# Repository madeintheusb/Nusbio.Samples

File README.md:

Nusbio Samples
===============

Nusbio is a USB device that brings 8 GPIO pins (General Purpose Input Output), to the .NET Runtime and programming languages C#, VB.NET, F# and IronPython (like the Raspberry PI GPIO row for C and Python).

Nusbio also offers: 

* 8 GPIO pins
* I2C and SPI support
* One unique serial number
* 32 bytes of EEPROM (.NET ASCII string 32 char)

* ADC (Analog to digital converter) with extension
* DAC (Digital to analog converter) with extension 
* Supported Devices: LCD, OLED, LED Matrix, Sensors, RGB LED,...

# Copyright

http://www.MadeInTheUSB.net

Copyright (C) 2015, 2016 MadeInTheUSB LLC

# License 

    All samples and components classes are released under the MIT License.

    Permission is hereby granted, free of charge, to any person obtaining a copy of this software and 
    associated documentation files (the "Software"), to deal in the Software without restriction, 
    including without limitation the rights to use, copy, modify, merge, publish, distribute, 
    sublicense, and/or sell copies of the Software, and to permit persons to whom the Software is 
    furnished to do so, subject to the following conditions:

    The above copyright notice and this permission notice shall be included in all copies or substantial 
    portions of the Software.

    THE SOFTWARE IS PROVIDED "AS IS", WITHOUT WARRANTY OF ANY KIND, EXPRESS OR IMPLIED, INCLUDING BUT NOT 
    LIMITED TO THE WARRANTIES OF MERCHANTABILITY, FITNESS FOR A PARTICULAR PURPOSE AND NONINFRINGEMENT. 
    IN NO EVENT SHALL THE AUTHORS OR COPYRIGHT HOLDERS BE LIABLE FOR ANY CLAIM, DAMAGES OR OTHER LIABILITY, 
    WHETHER IN AN ACTION OF CONTRACT, TORT OR OTHERWISE, ARISING FROM, OUT OF OR IN CONNECTION WITH THE SOFTWARE 
    OR THE USE OR OTHER DEALINGS IN THE SOFTWARE.

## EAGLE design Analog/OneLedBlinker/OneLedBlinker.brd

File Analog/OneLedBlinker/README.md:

One Led Blinker
===============

Copyright (C) 2015 MadeInTheUSB.net

http://www.MadeInTheUSB.net

# License

Creative Commons - Attribution-ShareAlike 2.5 Generic (CC BY-SA 2.5)

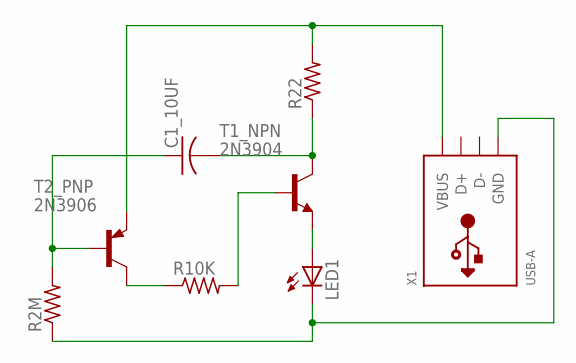
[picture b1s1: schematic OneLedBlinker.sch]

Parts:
C1_10UF: C-US025-030X050; C025-030X050
LED1: LED5MM
R2M, R10K, R22: R-US_0207/10; 0207/10
T1_NPN: 2N3904; TO92
T2_PNP: 2N3906; TO92
X1: USB-A; MOLEX_480371000

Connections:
unnamed: R22.2, T2_PNP.3 (E), X1.1 (VBUS)
unnamed: C1_10UF.2, R22.1, T1_NPN.1 (C)
unnamed: LED1.A, T1_NPN.3 (E)
unnamed: LED1.K (C), R2M.1, X1.4 (GND)
unnamed: C1_10UF.1, R2M.2, T2_PNP.2 (B)
unnamed: R10K.1, T2_PNP.1 (C)
unnamed: R10K.2, T1_NPN.2 (B)

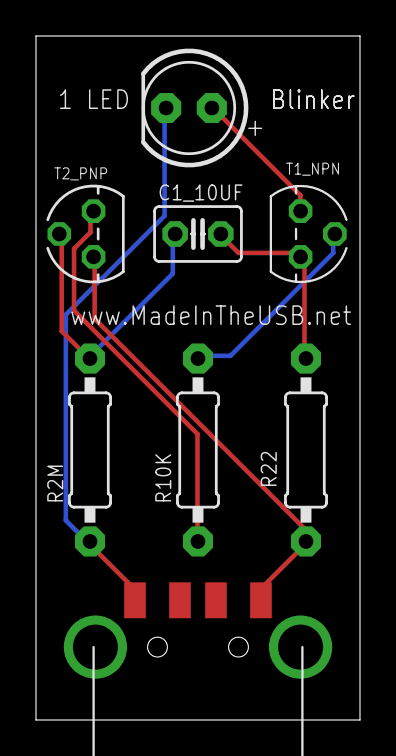
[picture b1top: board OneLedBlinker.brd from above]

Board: 2 copper layers, 18.0 x 38.0 mm, 8 parts (0 on the bottom side), 7 nets.

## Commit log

2016-04-07 :circus_tent: Added .gitattributes & .gitignore files
2016-04-07 Creation
2016-07-09 1.0.31 fixed web site on console
2016-07-09 1.0.32
2016-07-11 1.0.33
2016-07-11 Cleaning
2016-07-31 I2C interface cleaning and performance update
    I2C interface cleaning and performance update
2016-08-01 SPI clean up
2016-08-27 Change default addresss for I2C LCD
2016-08-28 improve transfer speed of i2c lcd
2016-11-25 Winter cleaning
2016-11-25 Create sub folder Adafruit
2016-12-18 Archive library for 2016
2017-01-01 Add Keypad project, fixed issue with I2C Adafruit 8x8 LED matrix related to support of Nusbio2
2017-01-25 New JoyStick and KeyPad sample, updated Nusbio library
2017-03-07 2015 trimester 1 update
    - NOR Flash support
    - SD Card support
    - New EEPROM support
    - Support of Nusbio2
2017-03-10 Powershell Motion Sensor Sample
2017-04-10 Added NUsbio.SPI.PrivateKeyManager
2017-04-14 Update for Analog demo, New MadeInTheUSB sFs
2017-04-17 update PrivateKeyManager and Sfs Console
2017-04-17 Decouple hardware access code from sFsManager.cs class
2017-04-17 Decouple console prompt command (AKA REPL) in it's own class
2017-06-03 Revisit chip 74HC595
2017-06-03 Update class ShiftRegister74HC595
2017-06-30 Added AT28C16 EEPROM programming and 7-Segment programming directly plugged into Nusbio
2017-07-09 7 segment sample, new Nusbio.lib version
2017-07-21 Update 7 segment code for extension
2017-08-24 moved file Nusbio.Samples-2016.zip
